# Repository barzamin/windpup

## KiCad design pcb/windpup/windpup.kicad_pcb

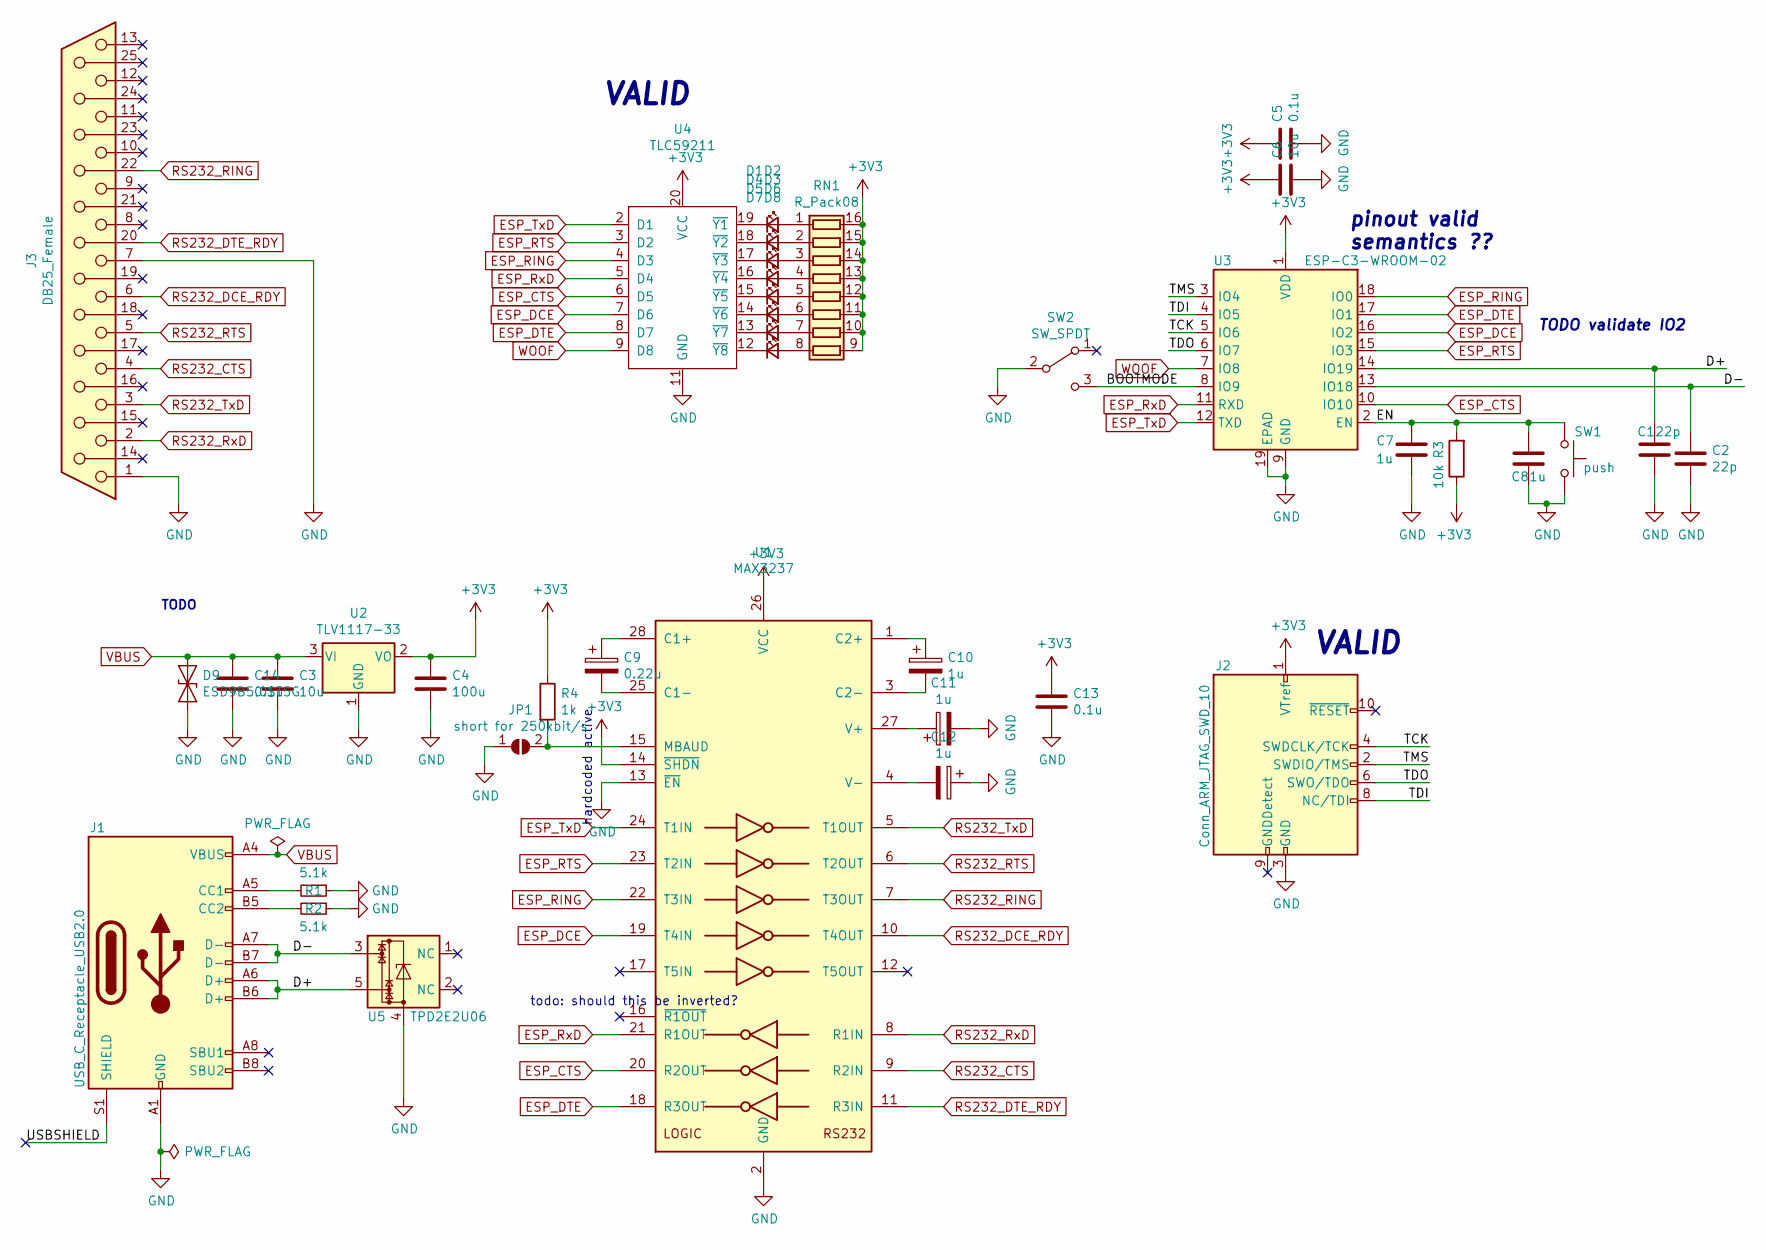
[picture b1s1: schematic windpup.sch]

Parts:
C1, C2: 22p; C_0805_2012Metric_Pad1.18x1.45mm_HandSolder
C3, C6: 10u; CP_EIA-3528-12_Kemet-T_Pad1.50x2.35mm_HandSolder
C4: 100u; CP_EIA-7343-31_Kemet-D_Pad2.25x2.55mm_HandSolder
C5, C13, C14: 0.1u; C_0805_2012Metric_Pad1.18x1.45mm_HandSolder
C7, C8, C10, C11, C12: 1u; C_0805_2012Metric_Pad1.18x1.45mm_HandSolder
C9: 0.22u; C_0805_2012Metric_Pad1.18x1.45mm_HandSolder
D1, D2, D3, D4, D5, D6, D7, D8: LED_Small; LED_0603_1608Metric_Pad1.05x0.95mm_HandSolder
D9: ESD9B5.0ST5G; D_SOD-923
J1: USB_C_Receptacle_USB2.0; USB_C_GCT_USB4085
J2: Conn_ARM_JTAG_SWD_10; PinHeader_2x05_P1.27mm_Vertical_SMD
J3: DB25_Female; DSUB-25_Female_EdgeMount_P2.77mm
JP1: short for 250kbit/s; SolderJumper-2_P1.3mm_Open_RoundedPad1.0x1.5mm
R1, R2: 5.1k; R_0805_2012Metric_Pad1.20x1.40mm_HandSolder
R3: 10k; R_0805_2012Metric_Pad1.20x1.40mm_HandSolder
R4: 1k; R_0805_2012Metric_Pad1.20x1.40mm_HandSolder
RN1: R_Pack08; R_Cat16-8
SW1: push; SW_Push_1P1T_NO_CK_KMR2
SW2: SW_SPDT; NidecCopal_CL-SB-12B-xx
U1: MAX3237; SSOP-28_5.3x10.2mm_P0.65mm
U2: TLV1117-33; TO-252-3_TabPin2
U3: ESP-C3-WROOM-02; ESP-WROOM-02
U4: TLC59211; TSSOP-20_4.4x6.5mm_P0.65mm
U5: TPD2E2U06; SOT-563

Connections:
+3V3: C4.1, C5.1, C6.1, C13.1, J2.1 (VTref), R3.1, R4.1, RN1.9 (R8.2), RN1.10 (R7.2), RN1.11 (R6.2), RN1.12 (R5.2), RN1.13 (R4.2), RN1.14 (R3.2), RN1.15 (R2.2), RN1.16 (R1.2), U1.14 (~SHDN), U1.26 (VCC), U2.2 (VO), U3.1 (VDD), U4.20 (VCC)
/BOOTMODE: SW2.3 (C), U3.8 (IO9)
/D+: C1.1, J1.A6 (D+), J1.B6 (D+), U3.14 (IO19), U5.5
/D-: C2.1, J1.A7 (D-), J1.B7 (D-), U3.13 (IO18), U5.3
/EN: C7.1, C8.1, R3.2, SW1.1, U3.2 (EN)
/TCK: J2.4 (SWDCLK/TCK), U3.5 (IO6)
/TDI: J2.8 (NC/TDI), U3.4 (IO5)
/TDO: J2.6 (SWO/TDO), U3.6 (IO7)
/TMS: J2.2 (SWDIO/TMS), U3.3 (IO4)
/USBSHIELD: J1.S1 (SHIELD)
ESP_CTS: U1.20 (R2OUT), U3.10 (IO10), U4.6 (D5)
ESP_DCE: U1.19 (T4IN), U3.16 (IO2), U4.7 (D6)
ESP_DTE: U1.18 (R3OUT), U3.17 (IO1), U4.8 (D7)
ESP_RING: U1.22 (T3IN), U3.18 (IO0), U4.4 (D3)
ESP_RTS: U1.23 (T2IN), U3.15 (IO3), U4.3 (D2)
ESP_RxD: U1.21 (R1OUT), U3.11 (RXD), U4.5 (D4)
ESP_TxD: U1.24 (T1IN), U3.12 (TXD), U4.2 (D1)
GND: C1.2, C2.2, C3.2, C4.2, C5.2, C6.2, C7.2, C8.2, C11.2, C12.1, C13.2, C14.2, D9.2 (A2), J1.A1 (GND), J1.A12 (GND), J1.B1 (GND), J1.B12 (GND), J2.3 (GND), J2.5 (GND), J3.1, J3.7, JP1.1 (A), R1.1, R2.1, SW1.2, SW2.2 (B), U1.2 (GND), U1.13 (~EN), U2.1 (GND), U3.9 (GND), U3.19 (EPAD), U4.11 (GND), U5.4
unnamed: C9.1, U1.28 (C1+)
unnamed: C9.2, U1.25 (C1-)
unnamed: C10.1, U1.1 (C2+)
unnamed: C10.2, U1.3 (C2-)
unnamed: C11.1, U1.27 (V+)
unnamed: C12.2, U1.4 (V-)
unnamed: D1.1 (K), U4.19 (~Y1)
unnamed: D1.2 (A), RN1.1 (R1.1)
unnamed: D2.1 (K), U4.18 (~Y2)
unnamed: D2.2 (A), RN1.2 (R2.1)
unnamed: D3.1 (K), U4.17 (~Y3)
unnamed: D3.2 (A), RN1.3 (R3.1)
unnamed: D4.1 (K), U4.16 (~Y4)
unnamed: D4.2 (A), RN1.4 (R4.1)
unnamed: D5.1 (K), U4.15 (~Y5)
unnamed: D5.2 (A), RN1.5 (R5.1)
unnamed: D6.1 (K), U4.14 (~Y6)
unnamed: D6.2 (A), RN1.6 (R6.1)
unnamed: D7.1 (K), U4.13 (~Y7)
unnamed: D7.2 (A), RN1.7 (R7.1)
unnamed: D8.1 (K), U4.12 (~Y8)
unnamed: D8.2 (A), RN1.8 (R8.1)
unnamed: J1.A5 (CC1), R1.2
unnamed: J1.B5 (CC2), R2.2
unnamed: JP1.2 (B), R4.2, U1.15 (MBAUD)
RS232_CTS: J3.4, U1.9 (R2IN)
RS232_DCE_RDY: J3.6, U1.10 (T4OUT)
RS232_DTE_RDY: J3.20, U1.11 (R3IN)
RS232_RING: J3.22, U1.7 (T3OUT)
RS232_RTS: J3.5, U1.6 (T2OUT)
RS232_RxD: J3.2, U1.8 (R1IN)
RS232_TxD: J3.3, U1.5 (T1OUT)
VBUS: C3.1, C14.1, D9.1 (A1), J1.A4 (VBUS), J1.A9 (VBUS), J1.B4 (VBUS), J1.B9 (VBUS), U2.3 (VI)
WOOF: U3.7 (IO8), U4.9 (D8)

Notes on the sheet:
TODO
hardcoded active
todo: should this be inverted?
VALID
pinout valid semantics ??
TODO validate IO2

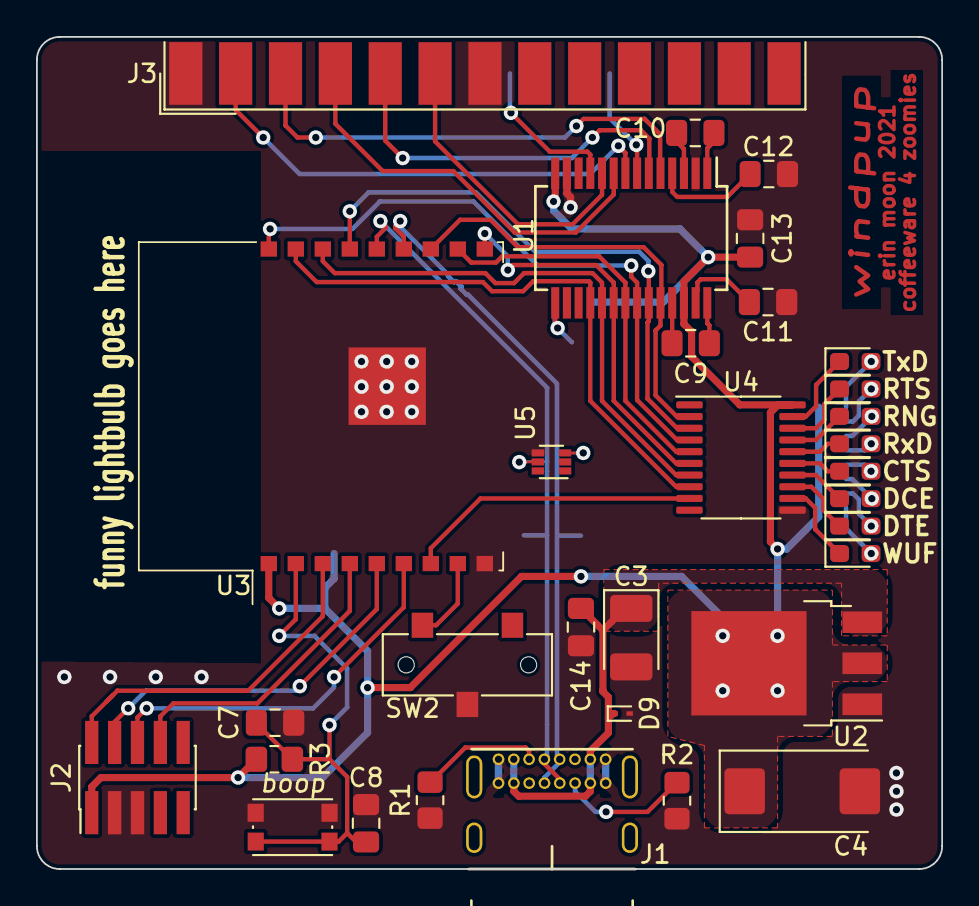
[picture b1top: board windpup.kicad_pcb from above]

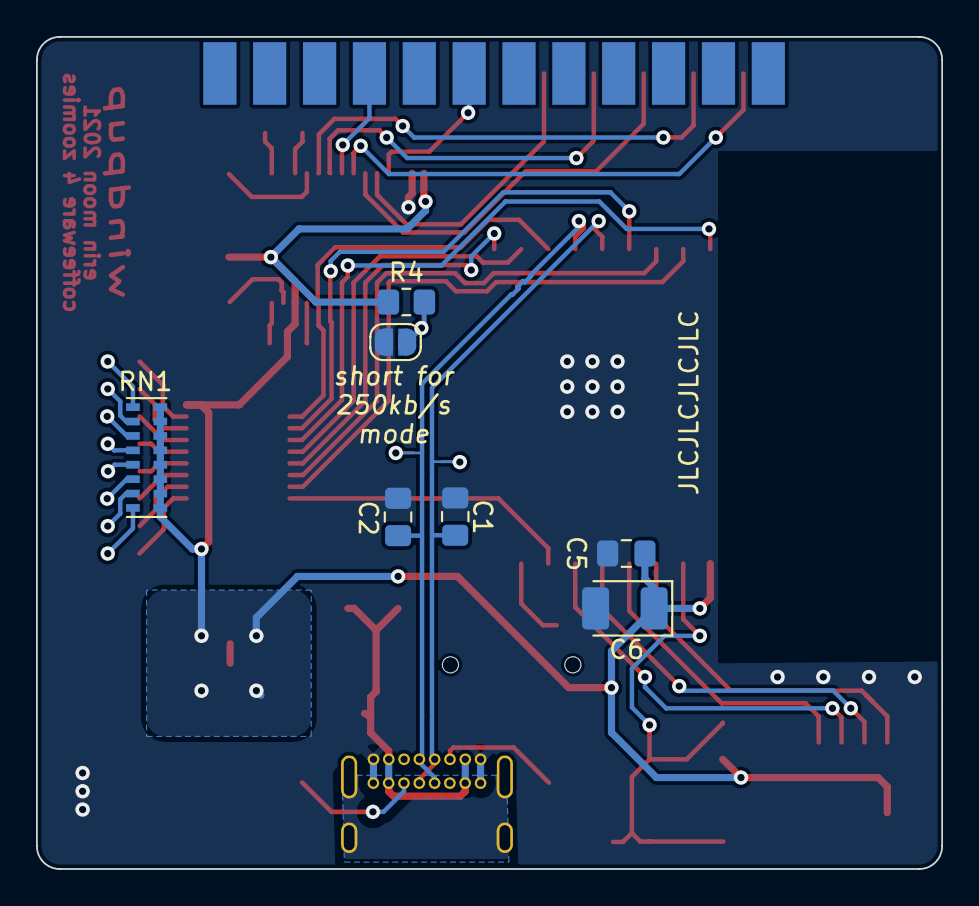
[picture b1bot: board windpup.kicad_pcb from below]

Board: 2 copper layers, 50.3 x 46.2 mm, 39 parts (7 on the bottom side), 51 nets.

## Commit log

2021-07-03 initial version
2021-07-23 pcb: update for manuf
2021-07-23 add boardrender
2021-07-23 initial firmware commit
2021-07-23 firmware: rename
2021-07-23 basic serial setup
2021-07-29 fw: blink WUF light
2021-07-29 start factory test
2021-08-06 factory test control line outputs
2021-08-06 add basic wifi sta functionality
2021-08-06 socket connection code
